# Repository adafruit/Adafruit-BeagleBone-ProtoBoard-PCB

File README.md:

## Adafruit Proto Cape Kit for Beagle Bone & Beagle Bone Black

<a href="http://www.adafruit.com/products/572"><br/>
Click here to purchase one from the Adafruit shop</a>

### Description

Add some circuitry to your Beagle Bone with our lovely Proto Cape. If you have a 'Bone you need one of these! This PCB fits neatly on top of a Beagle Bone, without getting in the way of the Ethernet jack, and provides a breakout to both 46 pin headers - with individual numbering to keep them straight. We also threw down some strips to access the 5V and 3V power supplies as well as two SMT breakouts, one for SOIC-8's and one for SOT-23's. 

Kit comes with a double-sided FR4 PCB and 3 sticks of header. You'll need to place the header into the Beagle Bone and then solder the Proto Cape PCB in place, but its very easy and should take only 10 minutes max even for beginners. __Beagle Bone is not included!__ We do have 'Bones in the shop available for purchase separately.

### License

Adafruit invests time and resources providing this open source design, please support Adafruit and open-source hardware by purchasing products from [Adafruit](https://www.adafruit.com)!

Designed by Limor Fried/Ladyada and Kevin Townsend for Adafruit Industries.

Creative Commons Attribution/Share-Alike, all text above must be included in any redistribution. See license.txt for additional details.

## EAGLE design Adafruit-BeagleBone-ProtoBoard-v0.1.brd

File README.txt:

Adafruit Proto Cape Kit for Beagle Bone 

These are the Eagle CAD files for the Adafruit Proto Cape Kit for Beagle Bone:
  ----> http://www.adafruit.com/products/572

Adafruit invests time and resources providing this open source design, please support Adafruit and open-source hardware by purchasing products from Adafruit!

Add some circuitry to your Beagle Bone with our lovely Proto Cape. If you have a 'Bone you need one of these! This PCB fits neatly on top of a Beagle Bone, without getting in the way of the Ethernet jack, and provides a breakout to both 46 pin headers - with individual numbering to keep them straight. We also threw down some strips to access the 5V and 3V power supplies as well as two SMT breakouts, one for SOIC-8's and one for SOT-23's. 

Kit comes with a double-sided FR4 PCB and 3 sticks of header. You'll need to place the header into the Beagle Bone and then solder the Proto Cape PCB in place, but its very easy and should take only 10 minutes max even for beginners

All text above must be included in any redistribution

Designed by Limor Fried/Ladyada and Kevin Townsend for Adafruit Industries.
Creative Commons Attribution/Share-Alike, all text above must be included in any redistribution

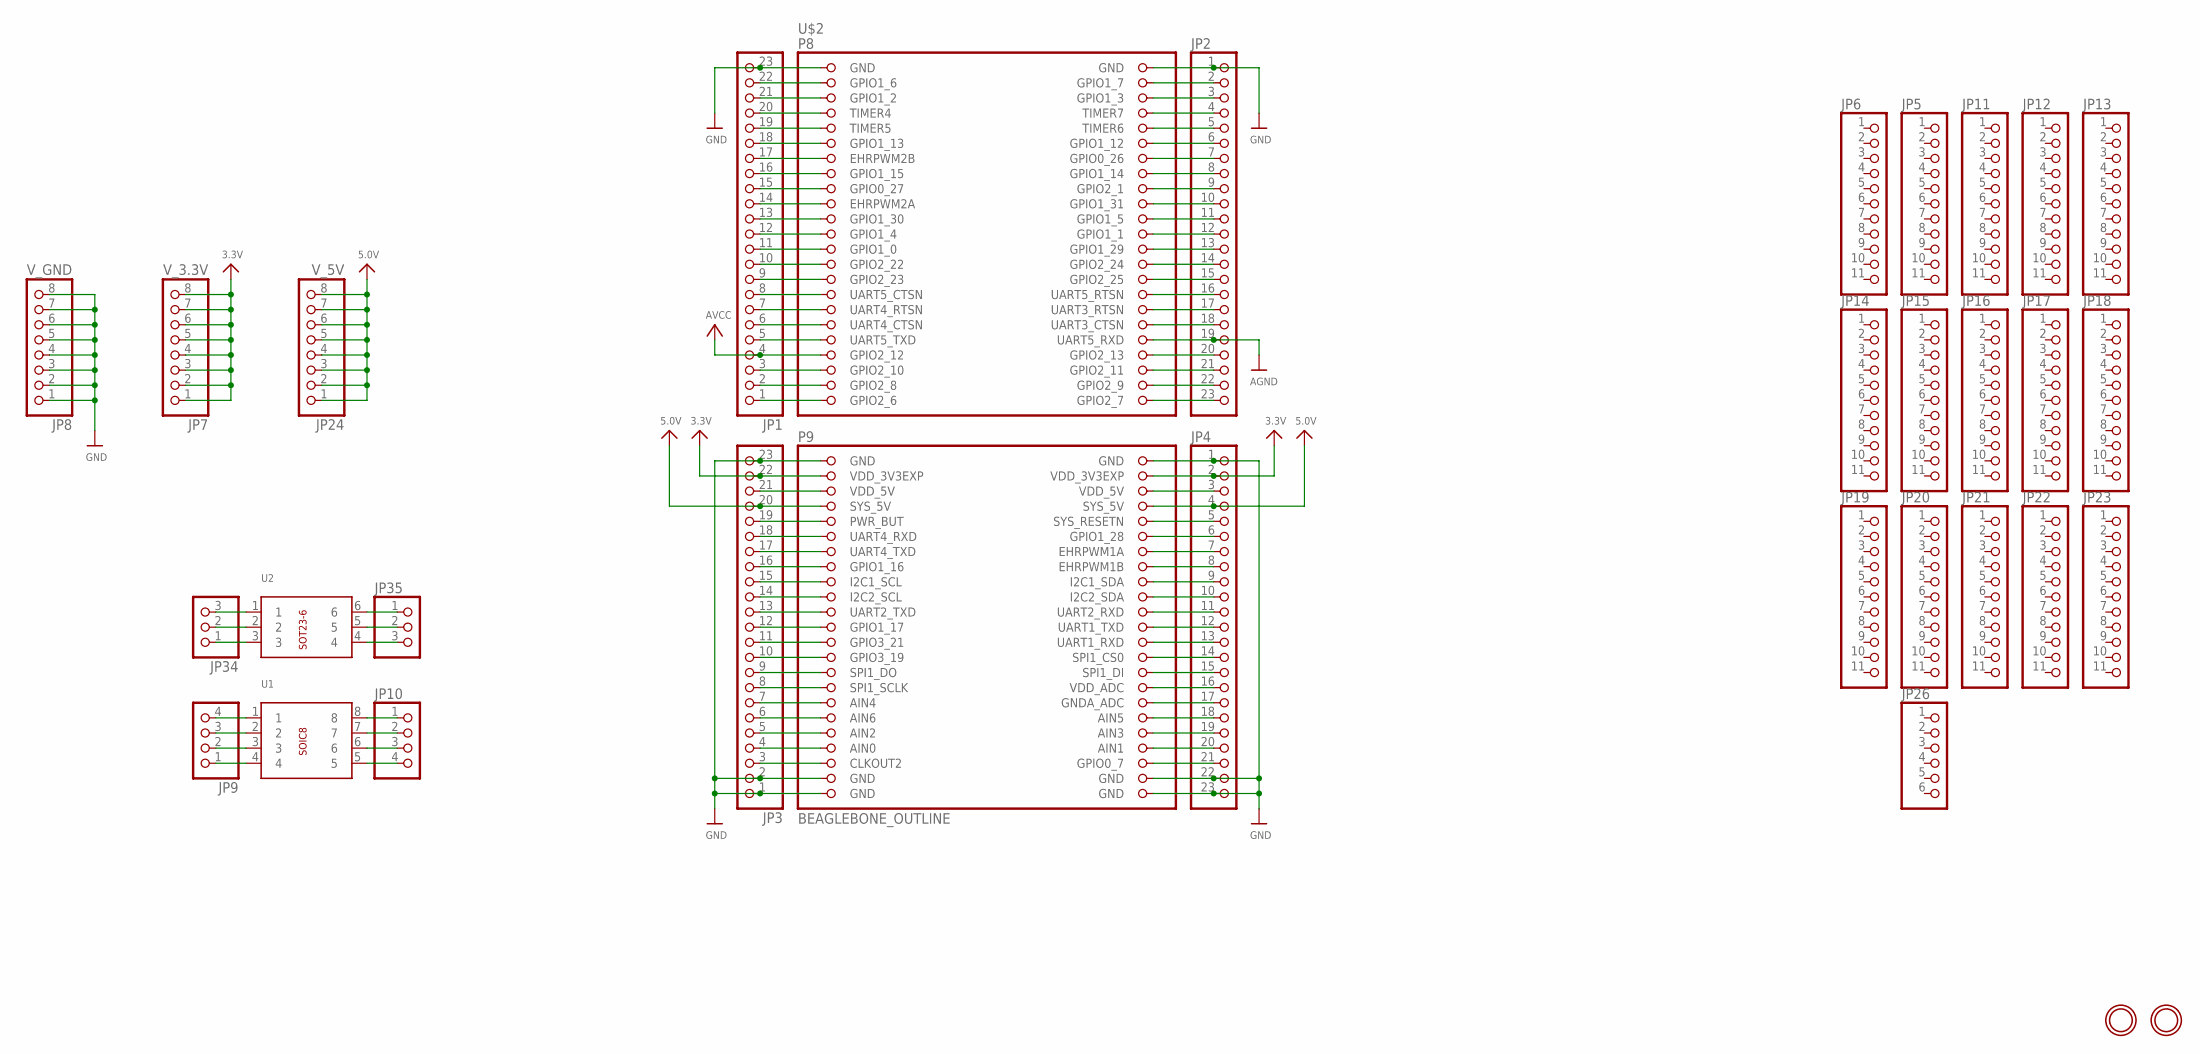
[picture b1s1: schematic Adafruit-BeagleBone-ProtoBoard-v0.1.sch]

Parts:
JP1, JP2, JP3, JP4: HEADER-1X23; 1X23_ROUND_70MIL
JP5, JP6, JP11, JP12, JP13, JP14, JP15, JP16, JP17, JP18, JP19, JP20, JP21, JP22, JP23: HEADER-1X1176MIL; 1X11_ROUND_76
JP7: V_3.3V; 1X08_ROUND_70
JP8: V_GND; 1X08_ROUND_70
JP9, JP10: HEADER-1X476MIL; 1X04_ROUND_76
JP24: V_5V; 1X08_ROUND_70
JP26: HEADER-1X676MIL; 1X06_ROUND_76
JP34, JP35: HEADER-1X376MIL; 1X03_ROUND_76
U1: BREAKOUT_SOIC8
U2: BREAKOUT_SOT23-6
U$2: BEAGLEBONE_OUTLINE; BEAGLEBONE_SHIELD
U$22, U$23: MOUNTINGHOLE3.0THIN; MOUNTINGHOLE_3.0_PLATEDTHIN

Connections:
3.3V: JP3.22, JP4.2, JP7.1, JP7.2, JP7.3, JP7.4, JP7.5, JP7.6, JP7.7, JP7.8, U$2.49 (VDD_3V3EXP), U$2.50 (VDD_3V3EXP)
5.0V: JP3.20, JP4.4, JP24.1, JP24.2, JP24.3, JP24.4, JP24.5, JP24.6, JP24.7, JP24.8, U$2.53 (SYS_5V), U$2.54 (SYS_5V)
AGND: JP2.19, U$2.38 (UART5_RXD)
AVCC: JP1.4, U$2.39 (GPIO2_12)
GND: JP1.23, JP2.1, JP3.1, JP3.2, JP3.23, JP4.1, JP4.22, JP4.23, JP8.1, JP8.2, JP8.3, JP8.4, JP8.5, JP8.6, JP8.7, JP8.8, U$2.1 (GND), U$2.2 (GND), U$2.47 (GND), U$2.48 (GND), U$2.89 (GND), U$2.90 (GND), U$2.91 (GND), U$2.92 (GND)
unnamed: JP9.4, U1.1
unnamed: JP9.3, U1.2
unnamed: JP9.2, U1.3
unnamed: JP1.20, U$2.7 (TIMER4)
unnamed: JP1.19, U$2.9 (TIMER5)
unnamed: JP1.18, U$2.11 (GPIO1_13)
unnamed: JP1.17, U$2.13 (EHRPWM2B)
unnamed: JP1.16, U$2.15 (GPIO1_15)
unnamed: JP1.15, U$2.17 (GPIO0_27)
unnamed: JP1.14, U$2.19 (EHRPWM2A)
unnamed: JP1.13, U$2.21 (GPIO1_30)
unnamed: JP1.12, U$2.23 (GPIO1_4)
unnamed: JP1.11, U$2.25 (GPIO1_0)
unnamed: JP1.10, U$2.27 (GPIO2_22)
unnamed: JP1.9, U$2.29 (GPIO2_23)
unnamed: JP1.8, U$2.31 (UART5_CTSN)
unnamed: JP1.7, U$2.33 (UART4_RTSN)
unnamed: JP1.6, U$2.35 (UART4_CTSN)
unnamed: JP1.5, U$2.37 (UART5_TXD)
unnamed: JP9.1, U1.4
unnamed: JP1.3, U$2.41 (GPIO2_10)
unnamed: JP1.2, U$2.43 (GPIO2_8)
unnamed: JP1.1, U$2.45 (GPIO2_6)
unnamed: JP10.1, U1.8
unnamed: JP10.2, U1.7
unnamed: JP10.3, U1.6
unnamed: JP2.4, U$2.8 (TIMER7)
unnamed: JP2.5, U$2.10 (TIMER6)
unnamed: JP2.6, U$2.12 (GPIO1_12)
unnamed: JP2.7, U$2.14 (GPIO0_26)
unnamed: JP2.8, U$2.16 (GPIO1_14)
unnamed: JP2.9, U$2.18 (GPIO2_1)
unnamed: JP2.10, U$2.20 (GPIO1_31)
unnamed: JP2.11, U$2.22 (GPIO1_5)
unnamed: JP2.12, U$2.24 (GPIO1_1)
unnamed: JP2.13, U$2.26 (GPIO1_29)
unnamed: JP2.14, U$2.28 (GPIO2_24)
unnamed: JP2.15, U$2.30 (GPIO2_25)
unnamed: JP2.16, U$2.32 (UART5_RTSN)
unnamed: JP2.17, U$2.34 (UART3_RTSN)
unnamed: JP2.18, U$2.36 (UART3_CTSN)
unnamed: JP10.4, U1.5
unnamed: JP2.20, U$2.40 (GPIO2_13)
unnamed: JP2.21, U$2.42 (GPIO2_11)
unnamed: JP2.22, U$2.44 (GPIO2_9)
unnamed: JP2.23, U$2.46 (GPIO2_7)
unnamed: JP1.22, U$2.3 (GPIO1_6)
unnamed: JP1.21, U$2.5 (GPIO1_2)
unnamed: JP3.21, U$2.51 (VDD_5V)
unnamed: JP2.2, U$2.4 (GPIO1_7)
unnamed: JP3.19, U$2.55 (PWR_BUT)
unnamed: JP3.18, U$2.57 (UART4_RXD)
unnamed: JP3.17, U$2.59 (UART4_TXD)
unnamed: JP3.16, U$2.61 (GPIO1_16)
unnamed: JP3.15, U$2.63 (I2C1_SCL)
unnamed: JP3.14, U$2.65 (I2C2_SCL)
unnamed: JP3.13, U$2.67 (UART2_TXD)
unnamed: JP3.12, U$2.69 (GPIO1_17)
unnamed: JP3.11, U$2.71 (GPIO3_21)
unnamed: JP3.10, U$2.73 (GPIO3_19)
unnamed: JP3.9, U$2.75 (SPI1_DO)
unnamed: JP3.8, U$2.77 (SPI1_SCLK)
unnamed: JP3.7, U$2.79 (AIN4)
unnamed: JP3.6, U$2.81 (AIN6)
unnamed: JP3.5, U$2.83 (AIN2)
unnamed: JP3.4, U$2.85 (AIN0)
unnamed: JP3.3, U$2.87 (CLKOUT2)
unnamed: JP2.3, U$2.6 (GPIO1_3)
unnamed: JP4.21, U$2.88 (GPIO0_7)
unnamed: JP4.3, U$2.52 (VDD_5V)
unnamed: JP4.5, U$2.56 (SYS_RESETN)
unnamed: JP4.6, U$2.58 (GPIO1_28)
unnamed: JP4.7, U$2.60 (EHRPWM1A)
unnamed: JP4.8, U$2.62 (EHRPWM1B)
unnamed: JP4.9, U$2.64 (I2C1_SDA)
unnamed: JP4.10, U$2.66 (I2C2_SDA)
unnamed: JP4.11, U$2.68 (UART2_RXD)
unnamed: JP4.12, U$2.70 (UART1_TXD)
unnamed: JP4.13, U$2.72 (UART1_RXD)
unnamed: JP4.14, U$2.74 (SPI1_CS0)
unnamed: JP4.15, U$2.76 (SPI1_DI)
unnamed: JP4.16, U$2.78 (VDD_ADC)
unnamed: JP4.17, U$2.80 (GNDA_ADC)
unnamed: JP4.18, U$2.82 (AIN5)
unnamed: JP4.19, U$2.84 (AIN3)
unnamed: JP4.20, U$2.86 (AIN1)
unnamed: JP34.3, U2.1
unnamed: JP34.2, U2.2
unnamed: JP34.1, U2.3
unnamed: JP35.1, U2.6
unnamed: JP35.2, U2.5
unnamed: JP35.3, U2.4

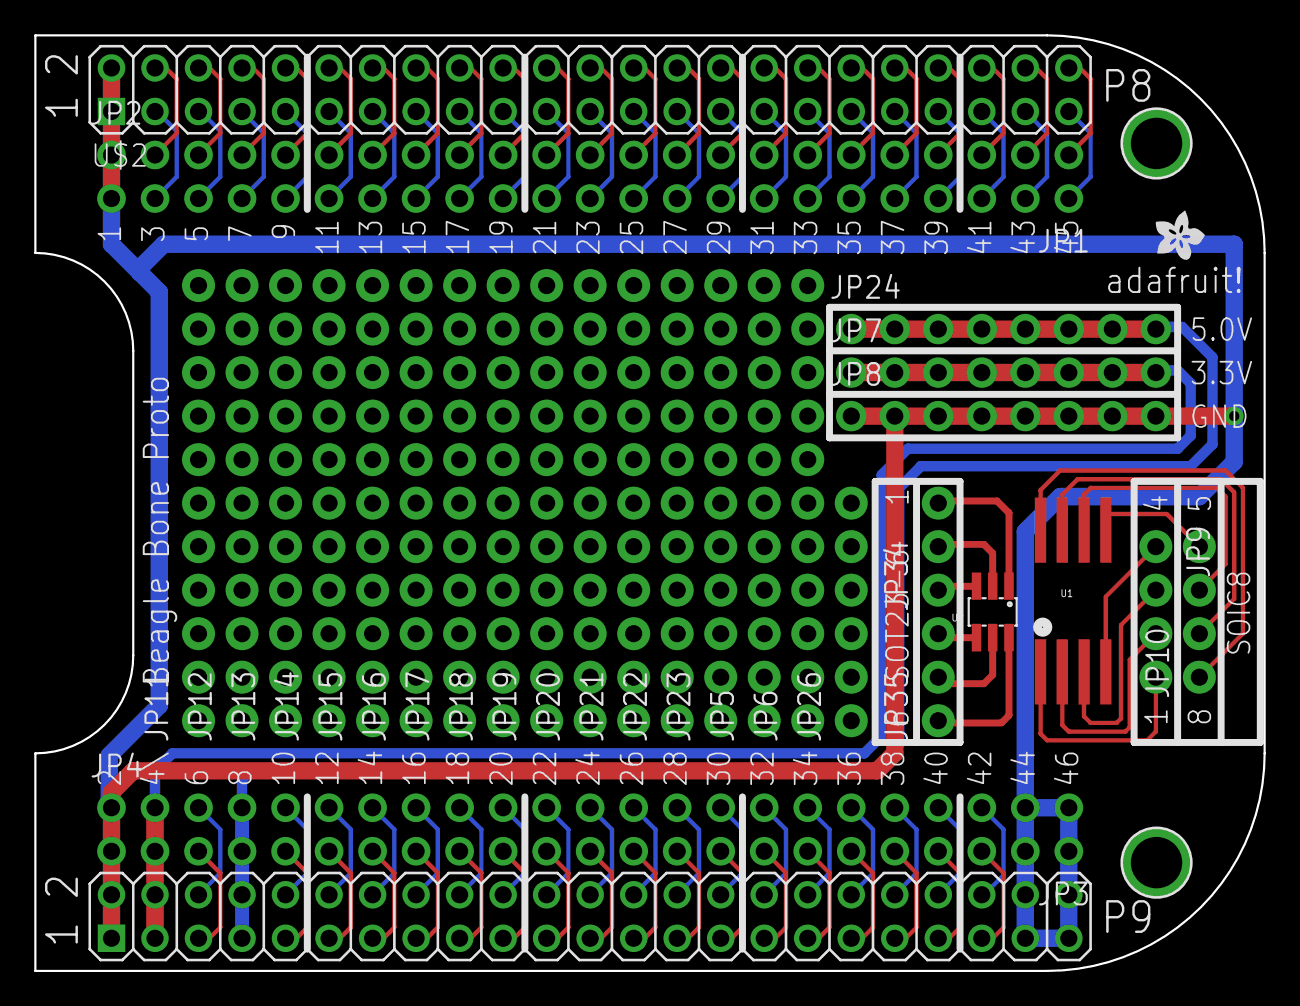
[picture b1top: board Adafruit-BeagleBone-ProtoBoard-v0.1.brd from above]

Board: 2 copper layers, 71.8 x 54.6 mm, 33 parts (0 on the bottom side), 97 nets.

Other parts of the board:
U$7: ADAFRUIT200MIL

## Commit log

2019-04-03 readme + image
2019-04-04 changed image
2026-06-03 update file format to XML
